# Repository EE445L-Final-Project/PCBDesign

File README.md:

# EE445L Final Project PCB Repository
This repository contains the schematics and board of the final design. For code part, please visit other repo.
## Note
This file format can only be opened by __Autodesk Eagle__.
## Download this Repository
```git clone https://github.com/EE445L-Final-Project/PCBDesign.git```

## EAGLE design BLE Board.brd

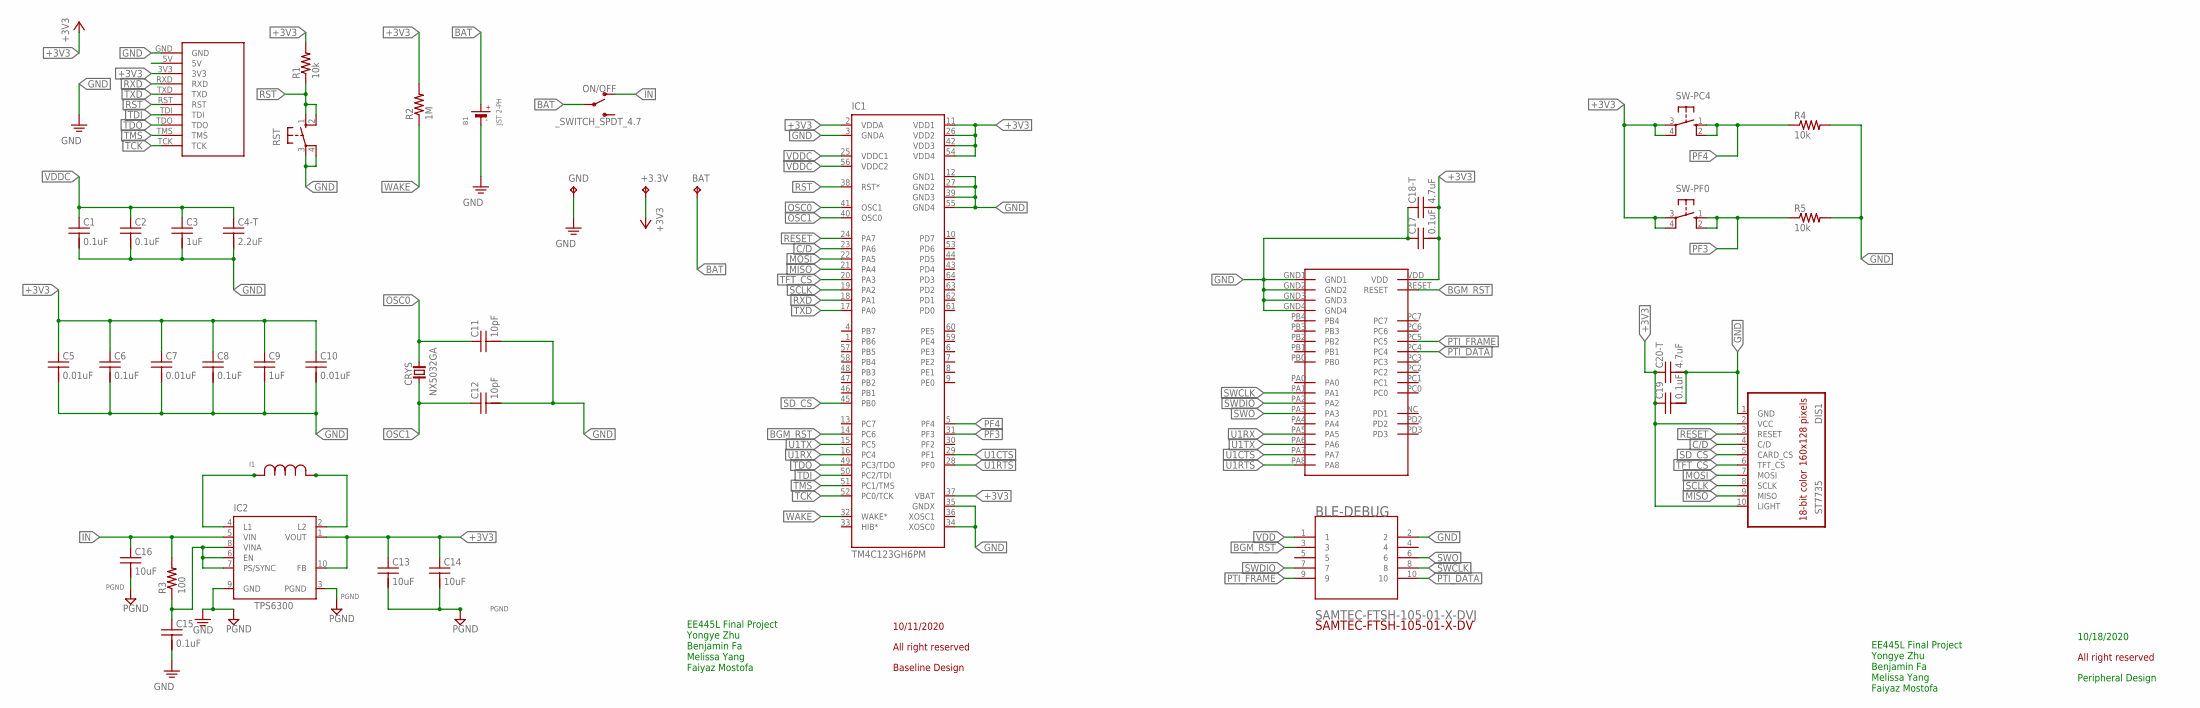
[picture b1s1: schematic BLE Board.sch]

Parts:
+3.3V: TP_KEYSTONE500X; P1.1MM
B1: JST 2-PH; JSTPH2
BAT: TP_KEYSTONE500X; P1.1MM
BLE: BGM220P
BLE-DEBUG: SAMTEC-FTSH-105-01-X-DVJ; SAMTEC-FTSH-105-01-X-DV
C1, C2, C6, C8, C15, C17, C19: 0.1uF; C0603K
C3, C9: 1uF; C0603K
C4-T: 2.2uF; C0603K
C5, C7, C10: 0.01uF; C0603K
C11, C12: 10pF; C0603K
C13, C14, C16: 10uF; C0603K
C18-T, C20-T: 4.7uF; C0603K
CRYS: NX5032GA; 2-SMD-5X3
DIS1: ST7735
GND: TP_KEYSTONE500X; P1.1MM
I1: IND_TPS; IND_LPS3015
IC1: TM4C123GH6PM; SQFP-S-10X10-64
IC2: TPS6300; DRC-S-PVSON-N10
JTAG: JTAG_SERIAL; JTAG_SERIAL_PTH
ON/OFF: _SWITCH_SPDT_4.7
R1, R4, R5: 10k; R0603
R2: 1M; R0603
R3: 100; R0603
RST: B3F-1052; B3F-10XX
SW-PC4: B3F-1052; B3F-10XX
SW-PF0: B3F-1052; B3F-10XX

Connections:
+3V3: +3.3V.TP, BLE.VDD, C5.1, C6.1, C7.1, C8.1, C9.1, C10.1, C13.1, C14.1, C17.2, C18-T.2, C19.1, C20-T.1, DIS1.2 (VCC), DIS1.10 (LIGHT), IC1.2 (VDDA), IC1.11 (VDD1), IC1.26 (VDD2), IC1.37 (VBAT), IC1.42 (VDD3), IC1.54 (VDD4), IC2.1 (VOUT), IC2.10 (FB), JTAG.3V3, R1.2, R2.2, SW-PC4.3, SW-PC4.4 (P1), SW-PF0.3, SW-PF0.4 (P1)
BAT: B1.2 (+), BAT.TP, ON/OFF.P$2
BGM_RST: BLE.RESET, BLE-DEBUG.3, IC1.14 (PC6)
C/D: DIS1.4 (C/D), IC1.23 (PA6)
GND: B1.1 (-), BLE.GND1, BLE.GND2, BLE.GND3, BLE.GND4, BLE-DEBUG.2, C1.2, C2.2, C3.2, C4-T.2, C5.2, C6.2, C7.2, C8.2, C9.2, C10.2, C11.2, C12.2, C15.2, C17.1, C18-T.1, C19.2, C20-T.2, DIS1.1 (GND), GND.TP, IC1.3 (GNDA), IC1.12 (GND1), IC1.27 (GND2), IC1.34 (XOSC0), IC1.35 (GNDX), IC1.39 (GND3), IC1.55 (GND4), IC2.9 (GND), JTAG.GND, R4.2, R5.2, RST.3, RST.4 (P1)
IN: C16.1, IC2.5 (VIN), ON/OFF.P$1 (O), R3.2
MISO: DIS1.9 (MISO), IC1.21 (PA4)
MOSI: DIS1.7 (MOSI), IC1.22 (PA5)
unnamed: C15.1, IC2.6 (EN), IC2.7 (PS/SYNC), IC2.8 (VINA), R3.1
unnamed: I1.2, IC2.4 (L1)
unnamed: I1.1, IC2.2 (L2)
OSC0: C11.1, CRYS.2, IC1.41 (OSC1)
OSC1: C12.1, CRYS.1, IC1.40 (OSC0)
PF3: IC1.31 (PF3), R5.1, SW-PF0.1 (S), SW-PF0.2 (S1)
PF4: IC1.5 (PF4), R4.1, SW-PC4.1 (S), SW-PC4.2 (S1)
PGND: C13.2, C14.2, C16.2, IC2.3 (PGND)
PTI_DATA: BLE.PC4, BLE-DEBUG.10
PTI_FRAME: BLE.PC5, BLE-DEBUG.9
RESET: DIS1.3 (RESET), IC1.24 (PA7)
RST: IC1.38 (RST*), JTAG.RST, R1.1, RST.1 (S), RST.2 (S1)
RXD: IC1.18 (PA1), JTAG.RXD
SCLK: DIS1.8 (SCLK), IC1.19 (PA2)
SD_CS: DIS1.5 (CARD_CS), IC1.45 (PB0)
SWCLK: BLE.PA1, BLE-DEBUG.8
SWDIO: BLE.PA2, BLE-DEBUG.7
SWO: BLE.PA3, BLE-DEBUG.6
TCK: IC1.52 (PC0/TCK), JTAG.TCK
TDI: IC1.50 (PC2/TDI), JTAG.TDI
TDO: IC1.49 (PC3/TDO), JTAG.TDO
TFT_CS: DIS1.6 (TFT_CS), IC1.20 (PA3)
TMS: IC1.51 (PC1/TMS), JTAG.TMS
TXD: IC1.17 (PA0), JTAG.TXD
U1CTS: BLE.PA7, IC1.29 (PF1)
U1RTS: BLE.PA8, IC1.28 (PF0)
U1RX: BLE.PA5, IC1.16 (PC4)
U1TX: BLE.PA6, IC1.15 (PC5)
VDD: BLE-DEBUG.1
VDDC: C1.1, C2.1, C3.1, C4-T.1, IC1.25 (VDDC1), IC1.56 (VDDC2)
WAKE: IC1.32 (WAKE*), R2.1

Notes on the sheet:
10/11/2020
All right reserved
Baseline Design
EE445L Final Project Yongye Zhu Benjamin Fa Melissa Yang Faiyaz Mostofa
Peripheral Design
10/18/2020

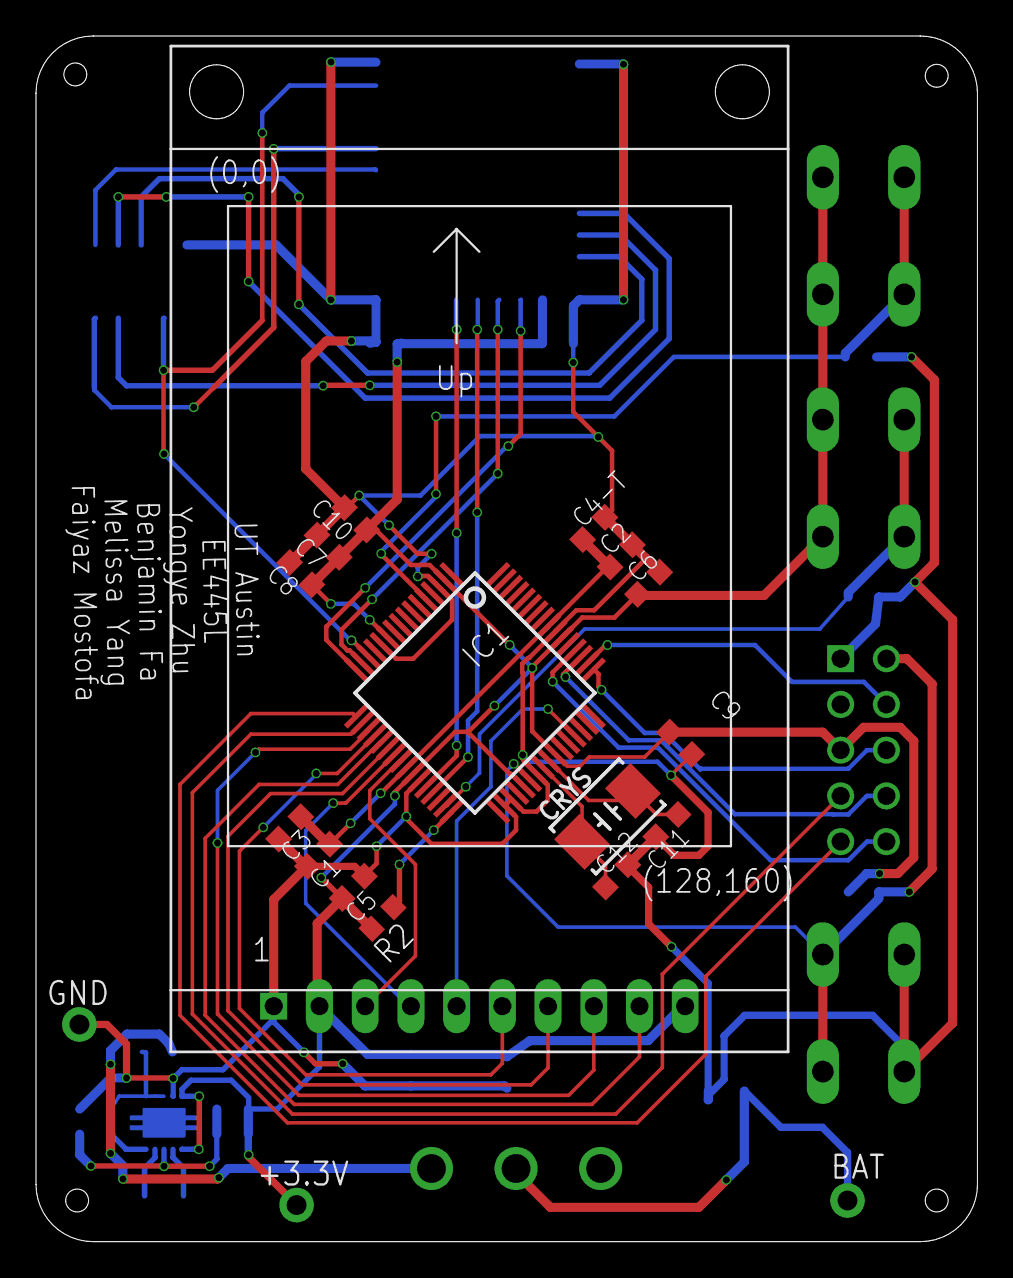
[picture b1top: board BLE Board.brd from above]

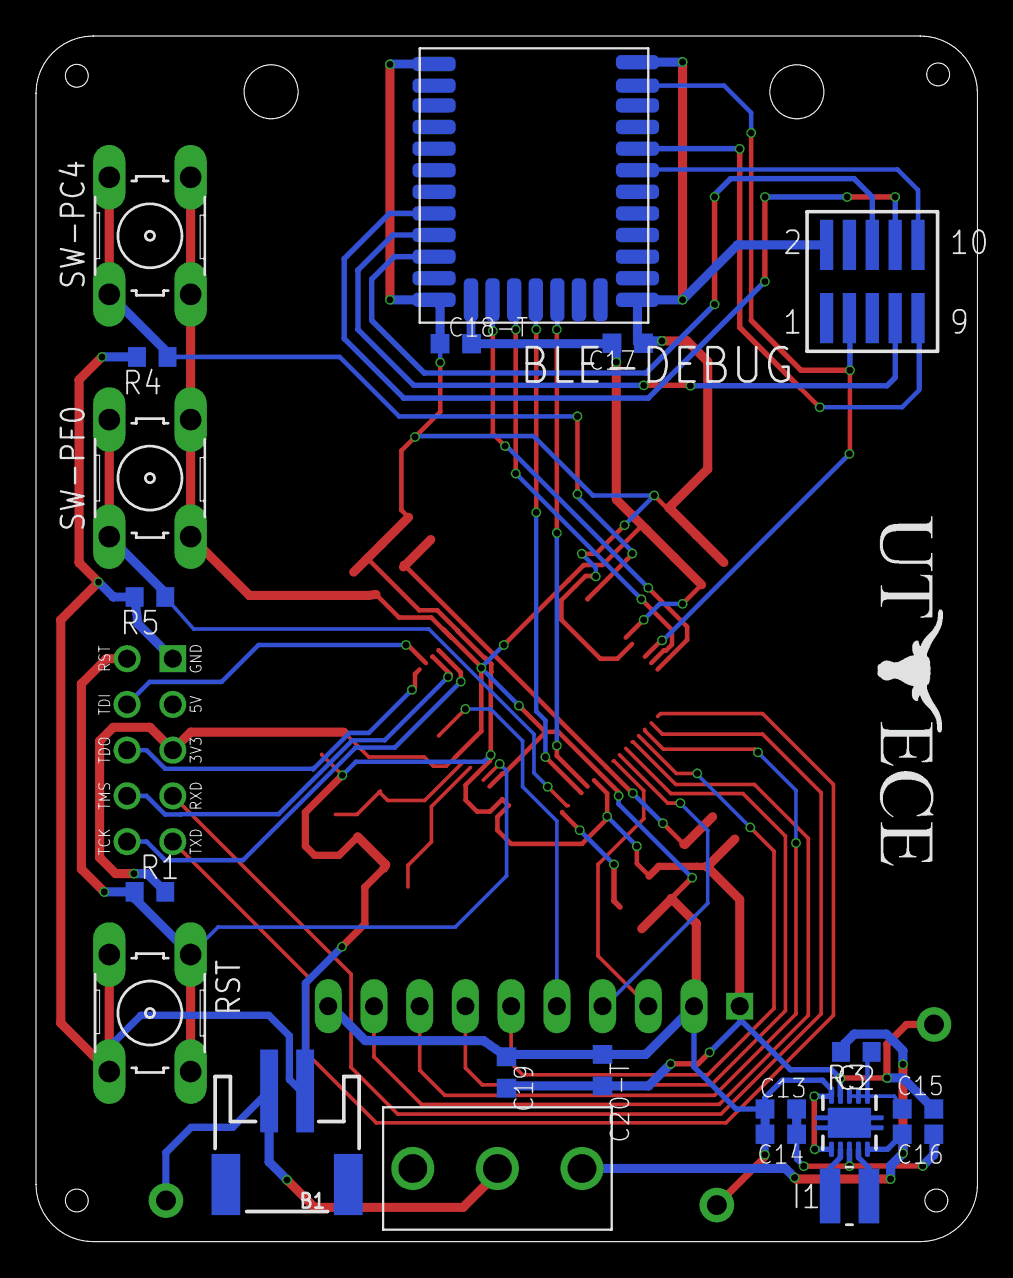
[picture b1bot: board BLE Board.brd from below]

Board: 2 copper layers, 52.3 x 67.0 mm, 42 parts (23 on the bottom side), 38 nets.

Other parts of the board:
U$1: __LOGO_UT_ECE

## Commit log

2020-10-18 First commit, add sch and brd file
2020-10-19 First arrangement of components
2020-10-19 revised BLE layout
2020-10-19 Flip the LCD
2020-10-19 Fix all errors
2020-10-20 First traces
2020-10-20 Add label
2020-10-22 Moved power reg., changed some parts
2020-10-22 Change button name on board
2020-10-22 0603 cap/res, add test pts for gnd/pwr
2020-10-26 Change direction of battery connector
2020-10-27 Fix wire issue
2020-10-27 Final Commit
2020-11-03 Added the Bottom Box files
    Working on the Top box right now
2020-11-03 Added the Box files
2020-11-03 Added LCD window to top

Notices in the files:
parts and their libraries:
microbuilder: This work is placed in the public domain, and may be freely used for commercial and non-commercial work with the following conditions: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
